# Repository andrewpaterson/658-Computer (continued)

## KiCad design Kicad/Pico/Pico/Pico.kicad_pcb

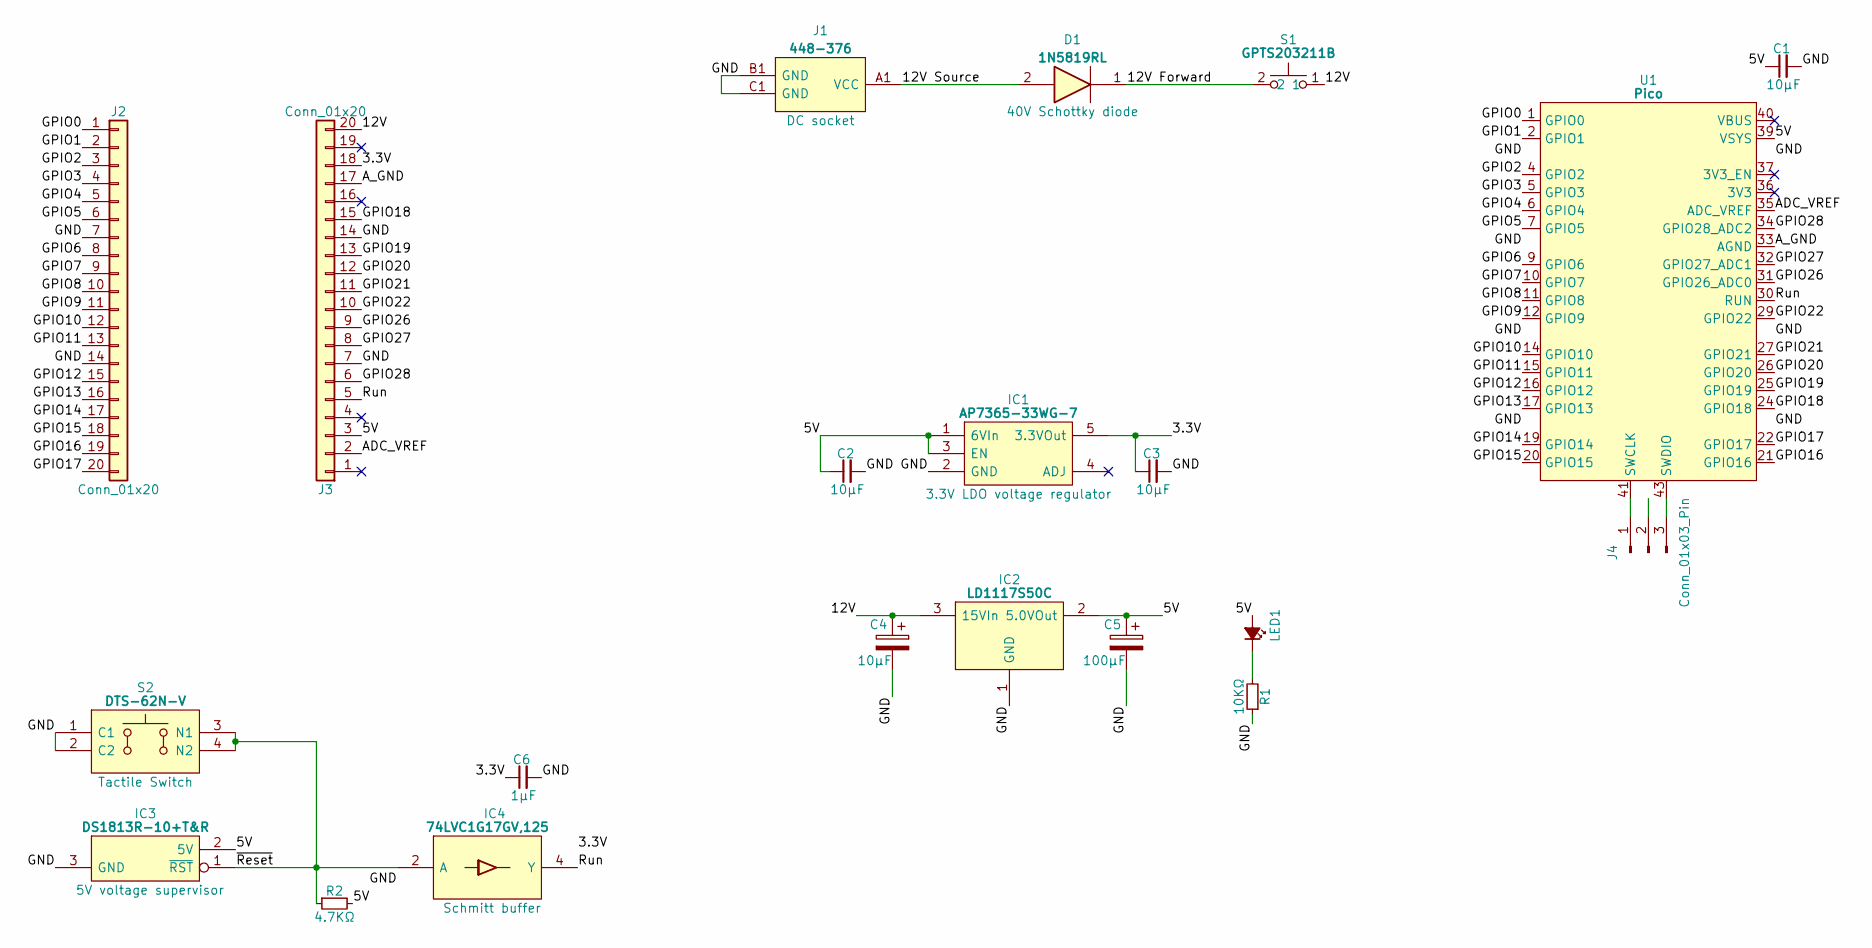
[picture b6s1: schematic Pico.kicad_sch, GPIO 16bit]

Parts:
C1: 10μF; C_0805
C2, C3: 10µF; C_0805
C4: 10μF; CP_Radial_D4.0mm_P2.00mm
C5: 100μF; CP_Radial_D4.0mm_P2.00mm
C6: 1μF; C_0805
D1: 1N5819RL; DIOAD1414W86L464D238; Manufacturer_Part_Number 1N5819RL; Mouser Part Number 511-1N5819-TR
IC1: AP7365-33WG-7; SOT95P285X130-5N; Manufacturer_Part_Number AP7365-33WG-7; Mouser Part Number 621-AP7365-33WG-7
IC2: LD1117S50C; LD1117S33C; Manufacturer_Part_Number LD1117S50C
IC3: DS1813R-10+T&R; SOT95P237X112-3N; Mouser Part Number 700-DS1813R-10T&R
IC4: 74LVC1G17GV,125; SOT95P275X110-5N; Manufacturer_Part_Number 74LVC1G17GV,125; Mouser Part Number 771-LVC1G17GV125
J1: 448-376; 448376; Manufacturer_Part_Number 448-376
J2, J3: Conn_01x20; SIP_20_Pins
J4: Conn_01x03_Pin; PinHeader_1x03_P2.54mm_Vertical
LED1: LED_Small_Filled; LED_D5.0mm
R1: 10KΩ; R_0805
R2: 4.7KΩ; R_0805
S1: GPTS203211B; Manufacturer_Part_Number GPTS203211B; Mouser Part Number 629-GPTS203211B
S2: DTS-62N-V; DTS62NV; Manufacturer_Part_Number DTS-62N-V; Mouser Part Number 113-DTS-62N-V
U1: Pico; RPi_Pico_SMD

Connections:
/3.3V: C3.1, C6.1, IC1.5 (3.3VOut), IC4.5 (3V), J3.18
/5V: C1.1, C2.1, C5.1, IC1.1 (6VIn), IC1.3 (EN), IC2.2 (5.0VOut), IC3.2 (5V), J3.3, LED1.2 (A), R2.2, U1.39 (VSYS)
/12V: C4.1, IC2.3 (15VIn), J3.20, S1.1
/12V Forward: D1.1, S1.2
/12V Source: D1.2, J1.A1 (VCC), J1.INNER (VCC)
/ADC_VREF: J3.2, U1.35 (ADC_VREF)
/A_GND: J3.17, U1.33 (AGND)
/GND: C1.2, C2.2, C3.2, C4.2, C5.2, C6.2, IC1.2 (GND), IC2.1 (GND), IC3.3 (GND), IC4.3 (GND), J1.B1 (GND), J1.C1 (GND), J1.SHL1 (GND), J1.SHL2 (GND), J2.7, J2.14, J3.7, J3.14, R1.1, S2.1 (C1), S2.2 (C2), U1.3 (GND), U1.8 (GND), U1.13 (GND), U1.18 (GND), U1.23 (GND), U1.28 (GND), U1.38 (GND)
/GPIO0: J2.1, U1.1 (GPIO0)
/GPIO1: J2.2, U1.2 (GPIO1)
/GPIO2: J2.3, U1.4 (GPIO2)
/GPIO3: J2.4, U1.5 (GPIO3)
/GPIO4: J2.5, U1.6 (GPIO4)
/GPIO5: J2.6, U1.7 (GPIO5)
/GPIO6: J2.8, U1.9 (GPIO6)
/GPIO7: J2.9, U1.10 (GPIO7)
/GPIO8: J2.10, U1.11 (GPIO8)
/GPIO9: J2.11, U1.12 (GPIO9)
/GPIO10: J2.12, U1.14 (GPIO10)
/GPIO11: J2.13, U1.15 (GPIO11)
/GPIO12: J2.15, U1.16 (GPIO12)
/GPIO13: J2.16, U1.17 (GPIO13)
/GPIO14: J2.17, U1.19 (GPIO14)
/GPIO15: J2.18, U1.20 (GPIO15)
/GPIO16: J2.19, U1.21 (GPIO16)
/GPIO17: J2.20, U1.22 (GPIO17)
/GPIO18: J3.15, U1.24 (GPIO18)
/GPIO19: J3.13, U1.25 (GPIO19)
/GPIO20: J3.12, U1.26 (GPIO20)
/GPIO21: J3.11, U1.27 (GPIO21)
/GPIO22: J3.10, U1.29 (GPIO22)
/GPIO26: J3.9, U1.31 (GPIO26_ADC0)
/GPIO27: J3.8, U1.32 (GPIO27_ADC1)
/GPIO28: J3.6, U1.34 (GPIO28_ADC2)
/Run: IC4.4 (Y), J3.5, U1.30 (RUN)
/~Reset: IC3.1 (~RST), IC4.2 (A), R2.1, S2.3 (N1), S2.4 (N2)
unnamed: J4.1, U1.41 (SWCLK)
unnamed: J4.2, U1.42 (GND)
unnamed: J4.3, U1.43 (SWDIO)
unnamed: LED1.1 (K), R1.2

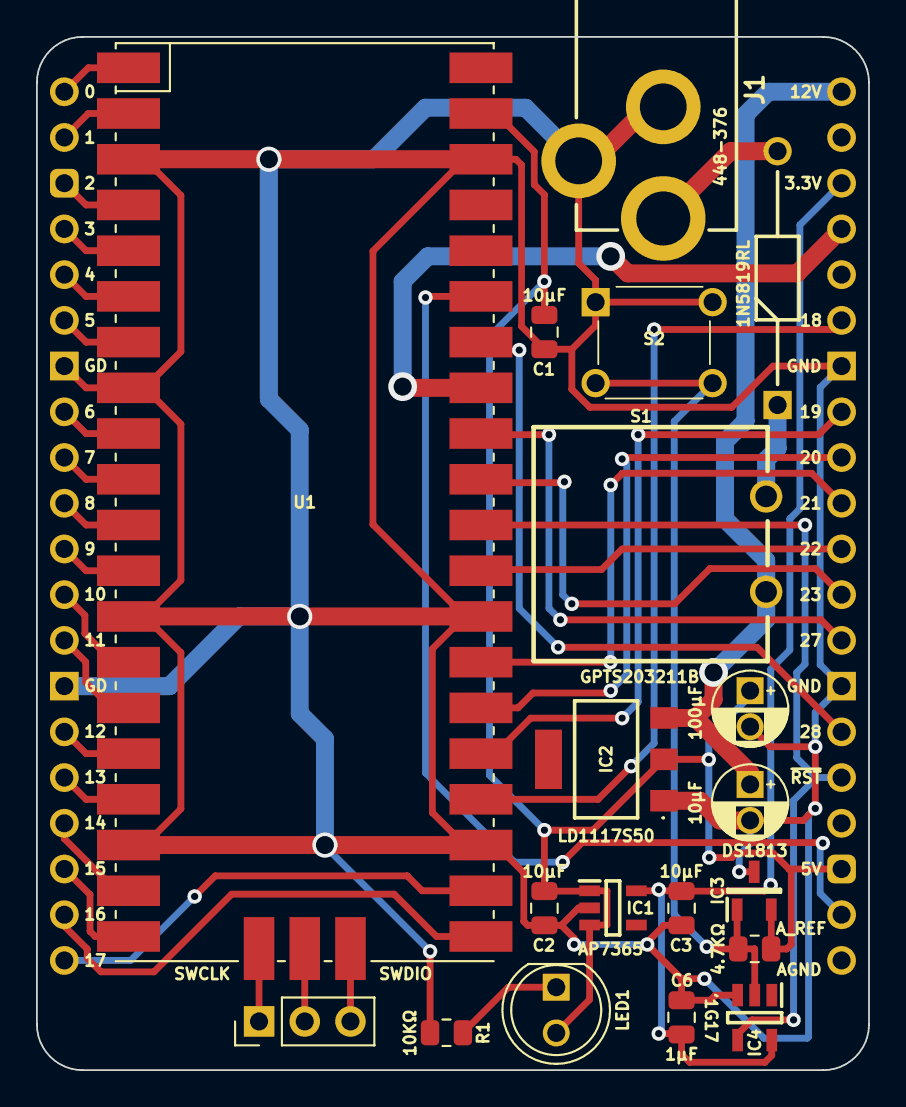
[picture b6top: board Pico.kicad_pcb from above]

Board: 2 copper layers, 46.2 x 57.4 mm, 21 parts (0 on the bottom side), 40 nets.

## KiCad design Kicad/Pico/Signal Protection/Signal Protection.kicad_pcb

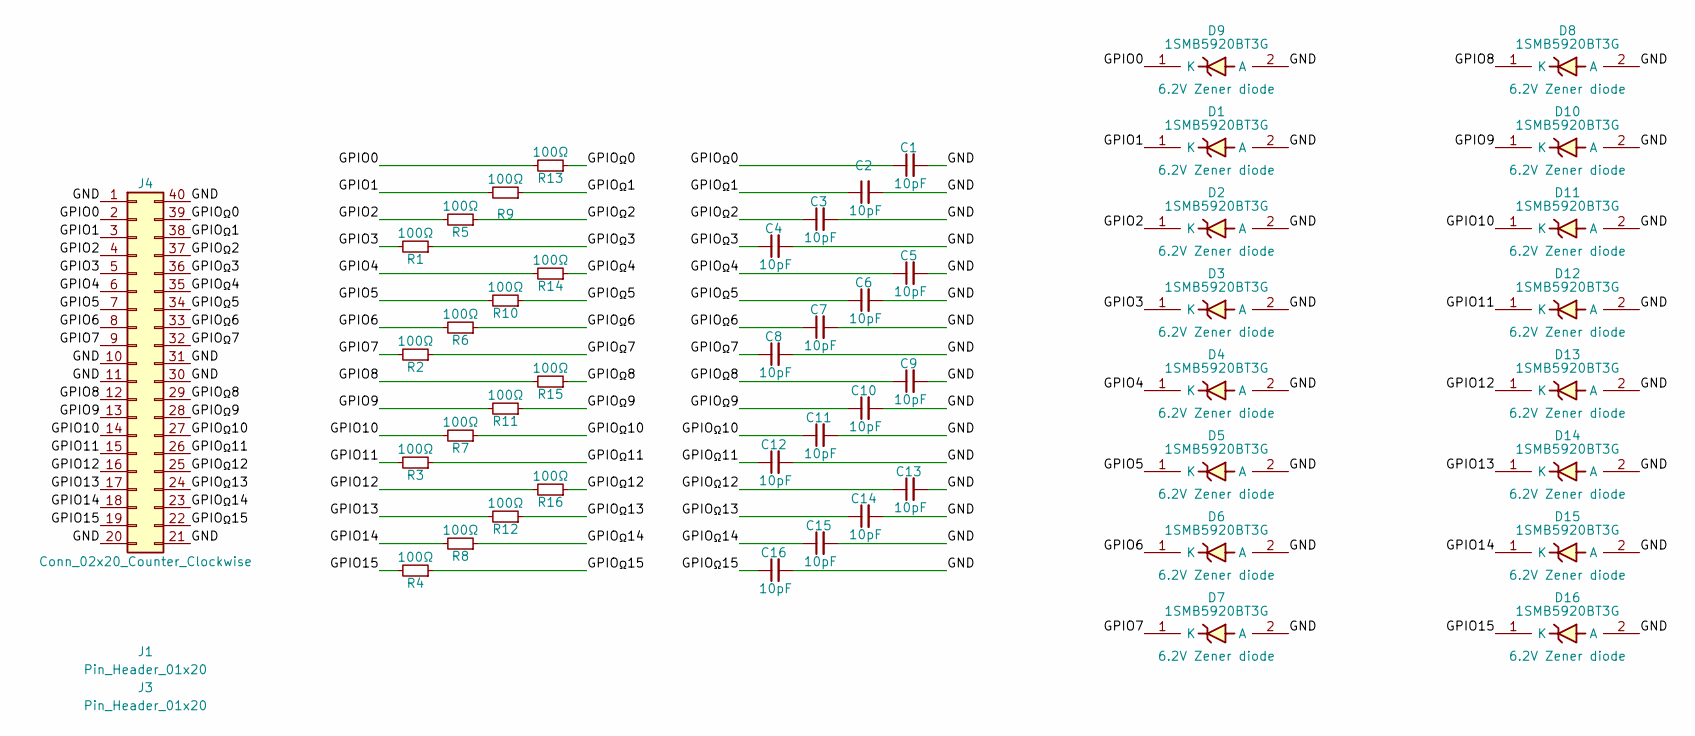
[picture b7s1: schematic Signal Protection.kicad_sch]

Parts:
C1, C2, C3, C4, C5, C6, C7, C8, C9, C10, C11, C12, C13, C14, C15, C16: 10pF; C_0805
D1, D2, D3, D4, D5, D6, D7, D8, D9, D10, D11, D12, D13, D14, D15, D16: 1SMB5920BT3G; DIOM5436X247N; Manufacturer_Part_Number 1SMB5920BT3G; Mouser Part Number 863-1SMB5920BT3G
J1, J3: Pin_Header_01x20; PinHeader_1x20_P2.54mm_Vertical
J4: Conn_02x20_Counter_Clockwise; DIP-40_Board_W22.86mm
R1, R2, R3, R4, R5, R6, R7, R8, R9, R10, R11, R12, R13, R14, R15, R16: 100Ω; RESC1630X53N

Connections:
/GND: C1.2, C2.2, C3.2, C4.2, C5.2, C6.2, C7.2, C8.2, C9.2, C10.2, C11.2, C12.2, C13.2, C14.2, C15.2, C16.2, D1.2 (A), D2.2 (A), D3.2 (A), D4.2 (A), D5.2 (A), D6.2 (A), D7.2 (A), D8.2 (A), D9.2 (A), D10.2 (A), D11.2 (A), D12.2 (A), D13.2 (A), D14.2 (A), D15.2 (A), D16.2 (A), J4.1, J4.10, J4.11, J4.20, J4.21, J4.30, J4.31, J4.40
/GPIO0: D9.1 (K), J4.2, R13.2
/GPIO1: D1.1 (K), J4.3, R9.2
/GPIO2: D2.1 (K), J4.4, R5.2
/GPIO3: D3.1 (K), J4.5, R1.2
/GPIO4: D4.1 (K), J4.6, R14.2
/GPIO5: D5.1 (K), J4.7, R10.2
/GPIO6: D6.1 (K), J4.8, R6.2
/GPIO7: D7.1 (K), J4.9, R2.2
/GPIO8: D8.1 (K), J4.12, R15.2
/GPIO9: D10.1 (K), J4.13, R11.2
/GPIO10: D11.1 (K), J4.14, R7.2
/GPIO11: D12.1 (K), J4.15, R3.2
/GPIO12: D13.1 (K), J4.16, R16.2
/GPIO13: D14.1 (K), J4.17, R12.2
/GPIO14: D15.1 (K), J4.18, R8.2
/GPIO15: D16.1 (K), J4.19, R4.2
/GPIO_{Ω}0: C1.1, J4.39, R13.1
/GPIO_{Ω}1: C2.1, J4.38, R9.1
/GPIO_{Ω}2: C3.1, J4.37, R5.1
/GPIO_{Ω}3: C4.1, J4.36, R1.1
/GPIO_{Ω}4: C5.1, J4.35, R14.1
/GPIO_{Ω}5: C6.1, J4.34, R10.1
/GPIO_{Ω}6: C7.1, J4.33, R6.1
/GPIO_{Ω}7: C8.1, J4.32, R2.1
/GPIO_{Ω}8: C9.1, J4.29, R15.1
/GPIO_{Ω}9: C10.1, J4.28, R11.1
/GPIO_{Ω}10: C11.1, J4.27, R7.1
/GPIO_{Ω}11: C12.1, J4.26, R3.1
/GPIO_{Ω}12: C13.1, J4.25, R16.1
/GPIO_{Ω}13: C14.1, J4.24, R12.1
/GPIO_{Ω}14: C15.1, J4.23, R8.1
/GPIO_{Ω}15: C16.1, J4.22, R4.1

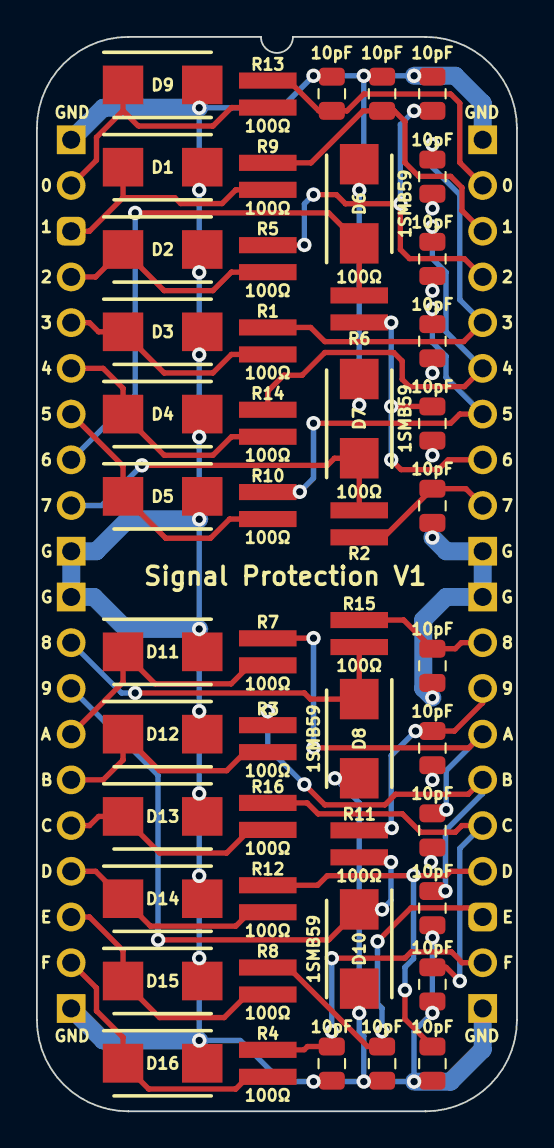
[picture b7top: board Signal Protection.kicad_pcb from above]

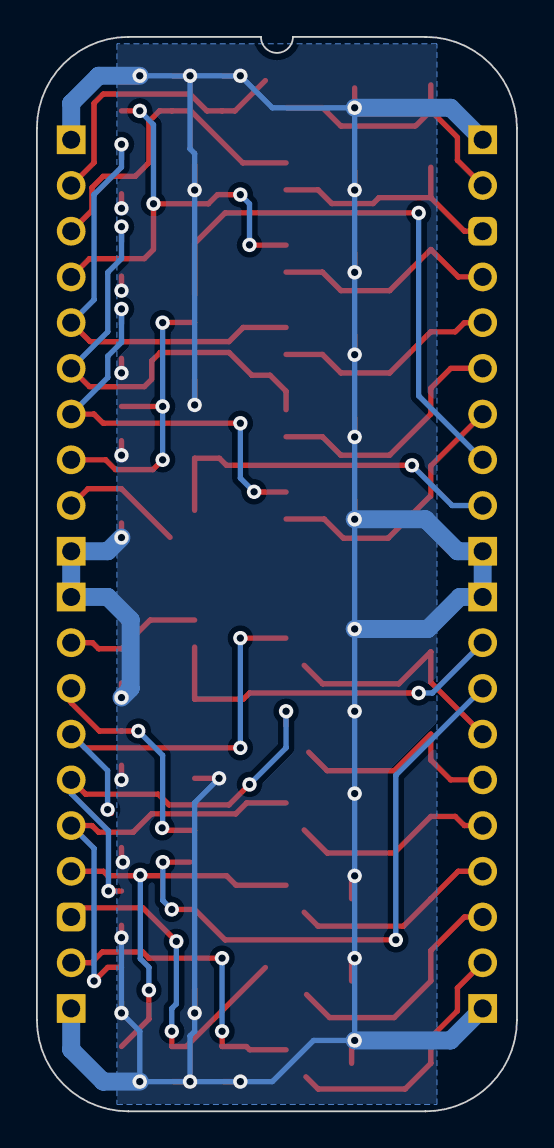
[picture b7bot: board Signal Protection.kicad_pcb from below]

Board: 2 copper layers, 26.7 x 59.7 mm, 51 parts (2 on the bottom side), 33 nets.

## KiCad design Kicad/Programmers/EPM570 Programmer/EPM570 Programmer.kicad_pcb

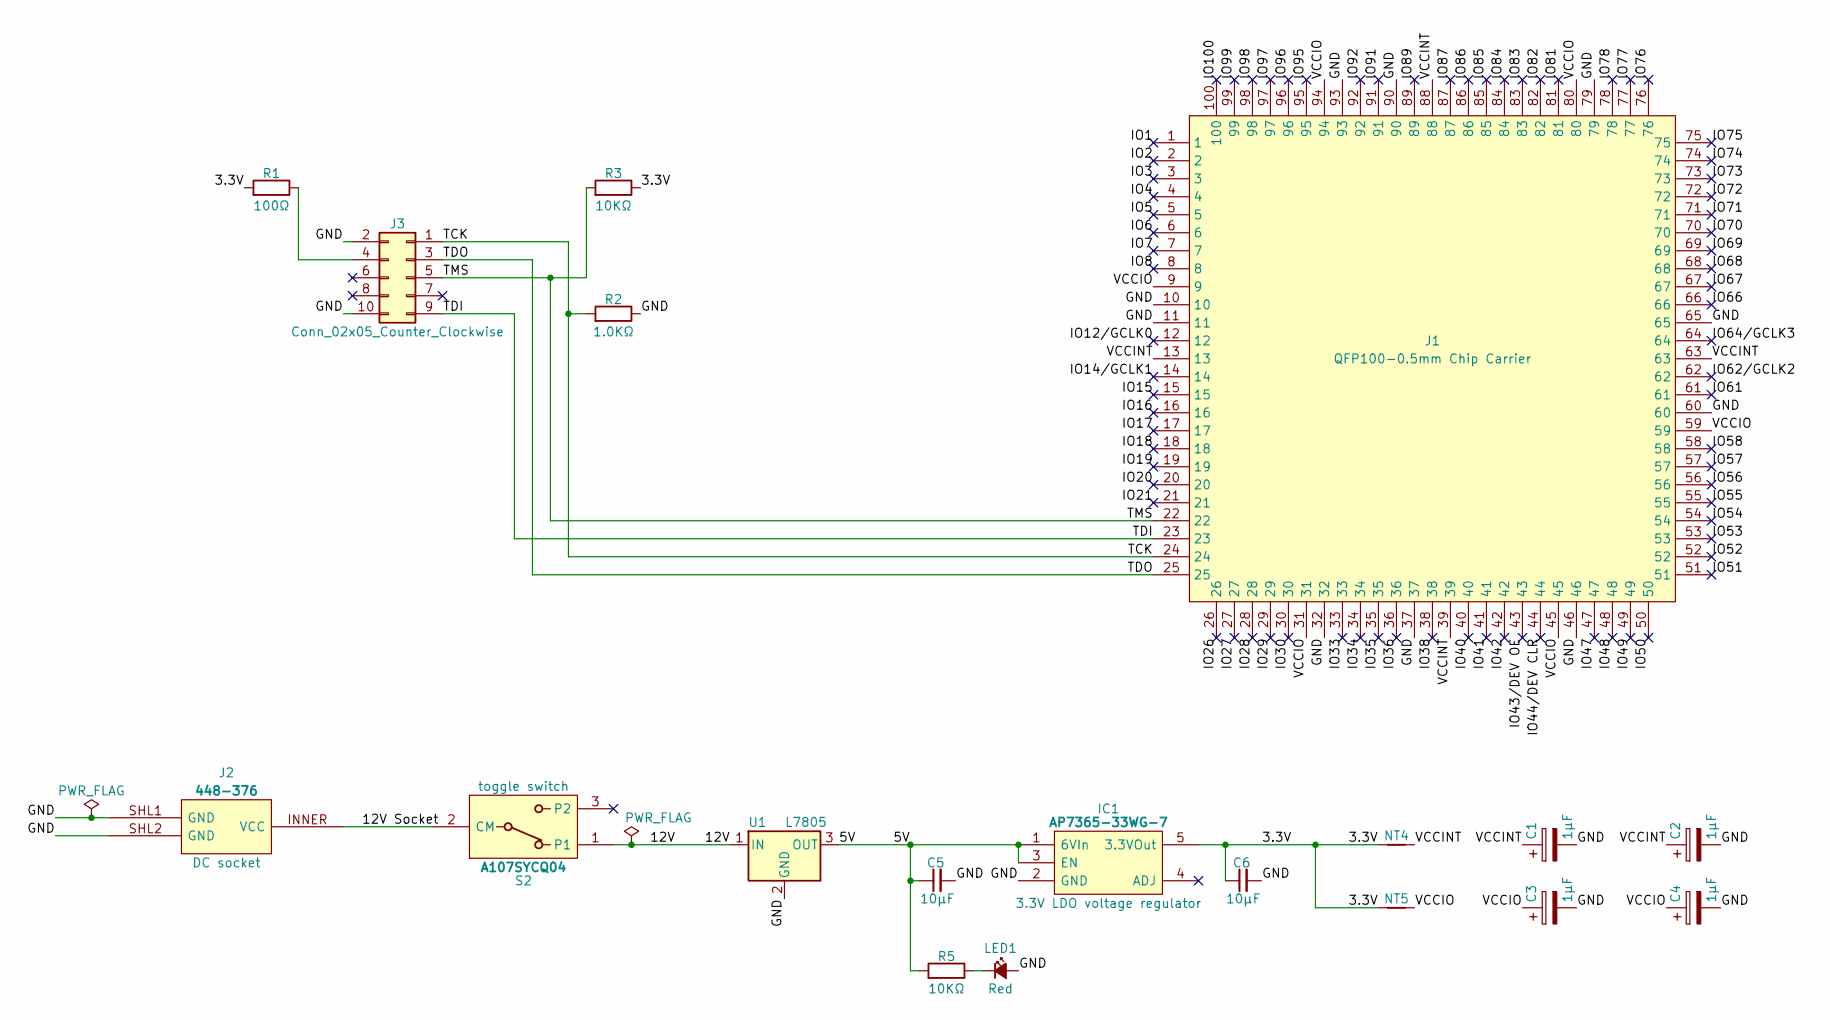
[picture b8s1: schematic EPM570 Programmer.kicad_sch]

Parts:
C1, C2, C3, C4: 1μF; CP_Radial_D4.0mm_P2.00mm
C5, C6: 10µF; C_0805
IC1: AP7365-33WG-7; SOT95P285X130-5N; Manufacturer_Part_Number AP7365-33WG-7; Mouser Part Number 621-AP7365-33WG-7
J1: AllSocket-QFP-100-14X14-0.5-Clamshell
J2: 448-376; 448376; Manufacturer_Part_Number 448-376
J3: Conn_02x05_Counter_Clockwise; PinHeader_2x05_P2.54mm_Vertical
LED1: Red; LED_D5.0mm
NT4, NT5: NetTie_2; NetTie-2_SMD_Pad0.5mm
R1: 100Ω; R_DIN_P12.70mm
R2: 1.0KΩ; R_DIN_P7.62mm
R3, R5: 10KΩ; R_DIN_P7.62mm
S2: A107SYCQ04; Manufacturer_Part_Number A107SYCQ04; Mouser Part Number 506-5-1825137-1
U1: L7805; TO-220-3_Vertical

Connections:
/3.3V: C6.1, IC1.5 (3.3VOut), NT4.1, NT5.1, R1.2, R3.1
/5V: C5.1, IC1.1 (6VIn), IC1.3 (EN), R5.2, U1.3 (OUT)
/12V: S2.1, U1.1 (IN)
/12V Socket: J2.INNER (VCC), S2.2 (CM)
/GND: C1.2, C2.2, C3.2, C4.2, C5.2, C6.2, IC1.2 (GND), J1.10, J1.11, J1.32, J1.37, J1.46, J1.60, J1.65, J1.79, J1.90, J1.93, J2.SHL1 (GND), J2.SHL2 (GND), J3.2, J3.10, LED1.2 (A), R2.1, U1.2 (GND)
/IO1: J1.1
/IO2: J1.2
/IO3: J1.3
/IO4: J1.4
/IO5: J1.5
/IO6: J1.6
/IO7: J1.7
/IO8: J1.8
/IO12/GCLK0: J1.12
/IO14/GCLK1: J1.14
/IO15: J1.15
/IO16: J1.16
/IO17: J1.17
/IO18: J1.18
/IO19: J1.19
/IO20: J1.20
/IO21: J1.21
/IO26: J1.26
/IO27: J1.27
/IO28: J1.28
/IO29: J1.29
/IO30: J1.30
/IO33: J1.33
/IO34: J1.34
/IO35: J1.35
/IO36: J1.36
/IO38: J1.38
/IO40: J1.40
/IO41: J1.41
/IO42: J1.42
/IO43/DEV OE: J1.43
/IO44/DEV CLR: J1.44
/IO47: J1.47
/IO48: J1.48
/IO49: J1.49
/IO50: J1.50
/IO51: J1.51
/IO52: J1.52
/IO53: J1.53
/IO54: J1.54
/IO55: J1.55
/IO56: J1.56
/IO57: J1.57
/IO58: J1.58
/IO61: J1.61
/IO62/GCLK2: J1.62
/IO64/GCLK3: J1.64
/IO66: J1.66
/IO67: J1.67
/IO68: J1.68
/IO69: J1.69
/IO70: J1.70
/IO71: J1.71
/IO72: J1.72
/IO73: J1.73
/IO74: J1.74
/IO75: J1.75
/IO76: J1.76
/IO77: J1.77
/IO78: J1.78
/IO81: J1.81
/IO82: J1.82
/IO83: J1.83
/IO84: J1.84
/IO85: J1.85
/IO86: J1.86
/IO87: J1.87
/IO89: J1.89
/IO91: J1.91
/IO92: J1.92
/IO95: J1.95
/IO96: J1.96
/IO97: J1.97
/IO98: J1.98
/IO99: J1.99
/IO100: J1.100
/TCK: J1.24, J3.1, R2.2
/TDI: J1.23, J3.9
/TDO: J1.25, J3.3
/TMS: J1.22, J3.5, R3.2
/VCCINT: C1.1, C2.1, J1.13, J1.39, J1.63, J1.88, NT4.2
/VCCIO: C3.1, C4.1, J1.9, J1.31, J1.45, J1.59, J1.80, J1.94, NT5.2
unnamed: J3.4, R1.1
unnamed: LED1.1 (K), R5.1

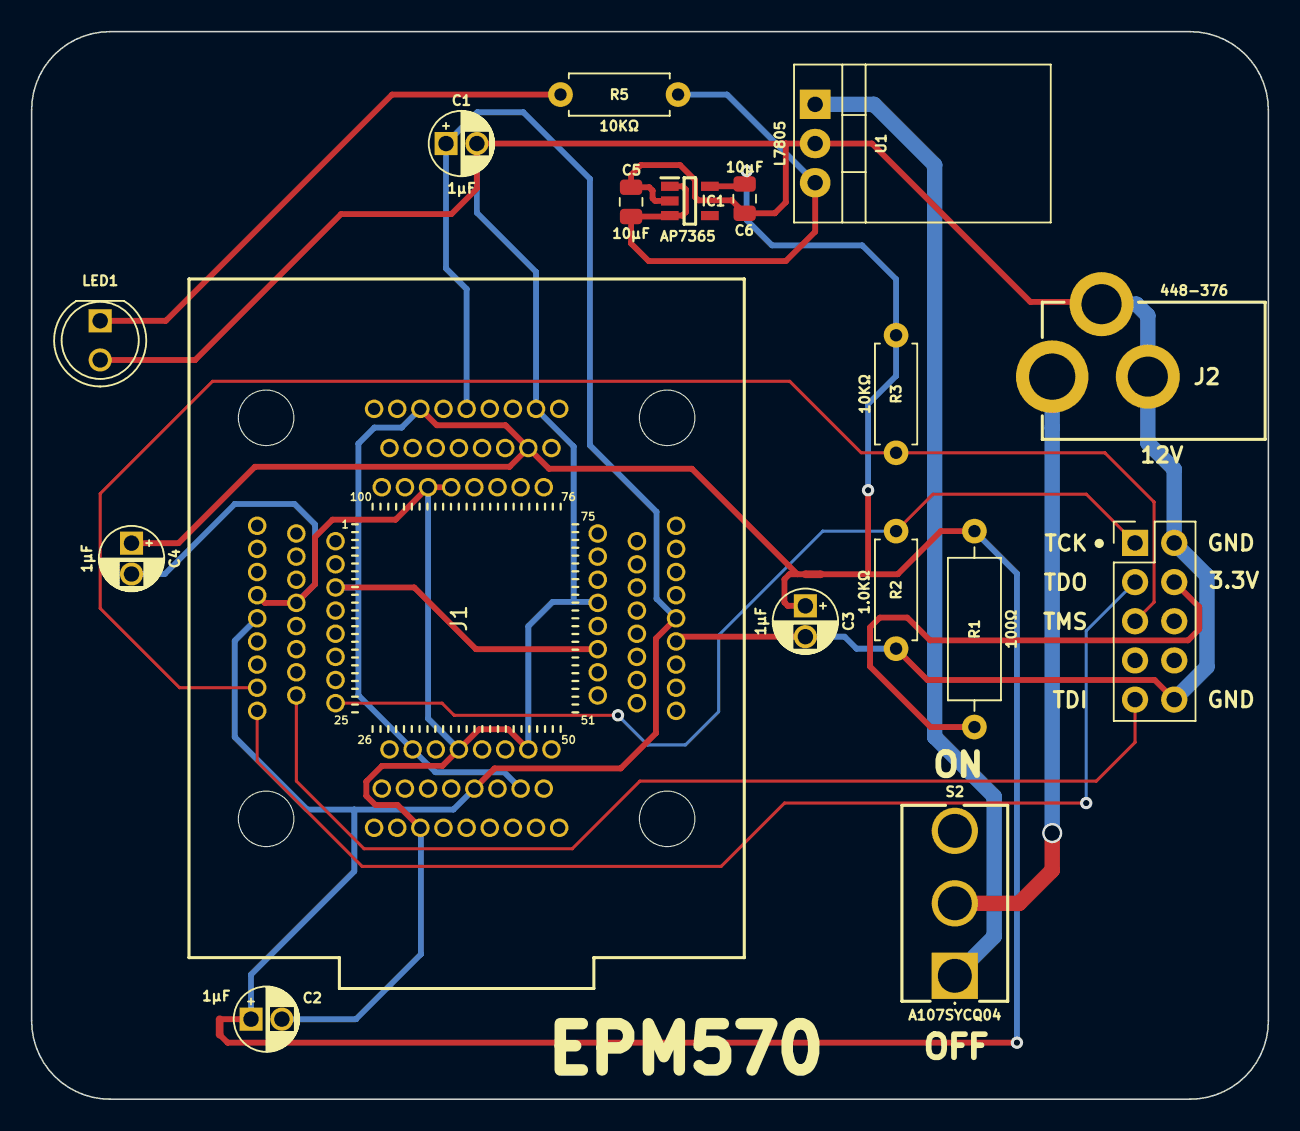
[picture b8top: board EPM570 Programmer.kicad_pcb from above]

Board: 2 copper layers, 80.2 x 69.2 mm, 19 parts (0 on the bottom side), 13 nets.
